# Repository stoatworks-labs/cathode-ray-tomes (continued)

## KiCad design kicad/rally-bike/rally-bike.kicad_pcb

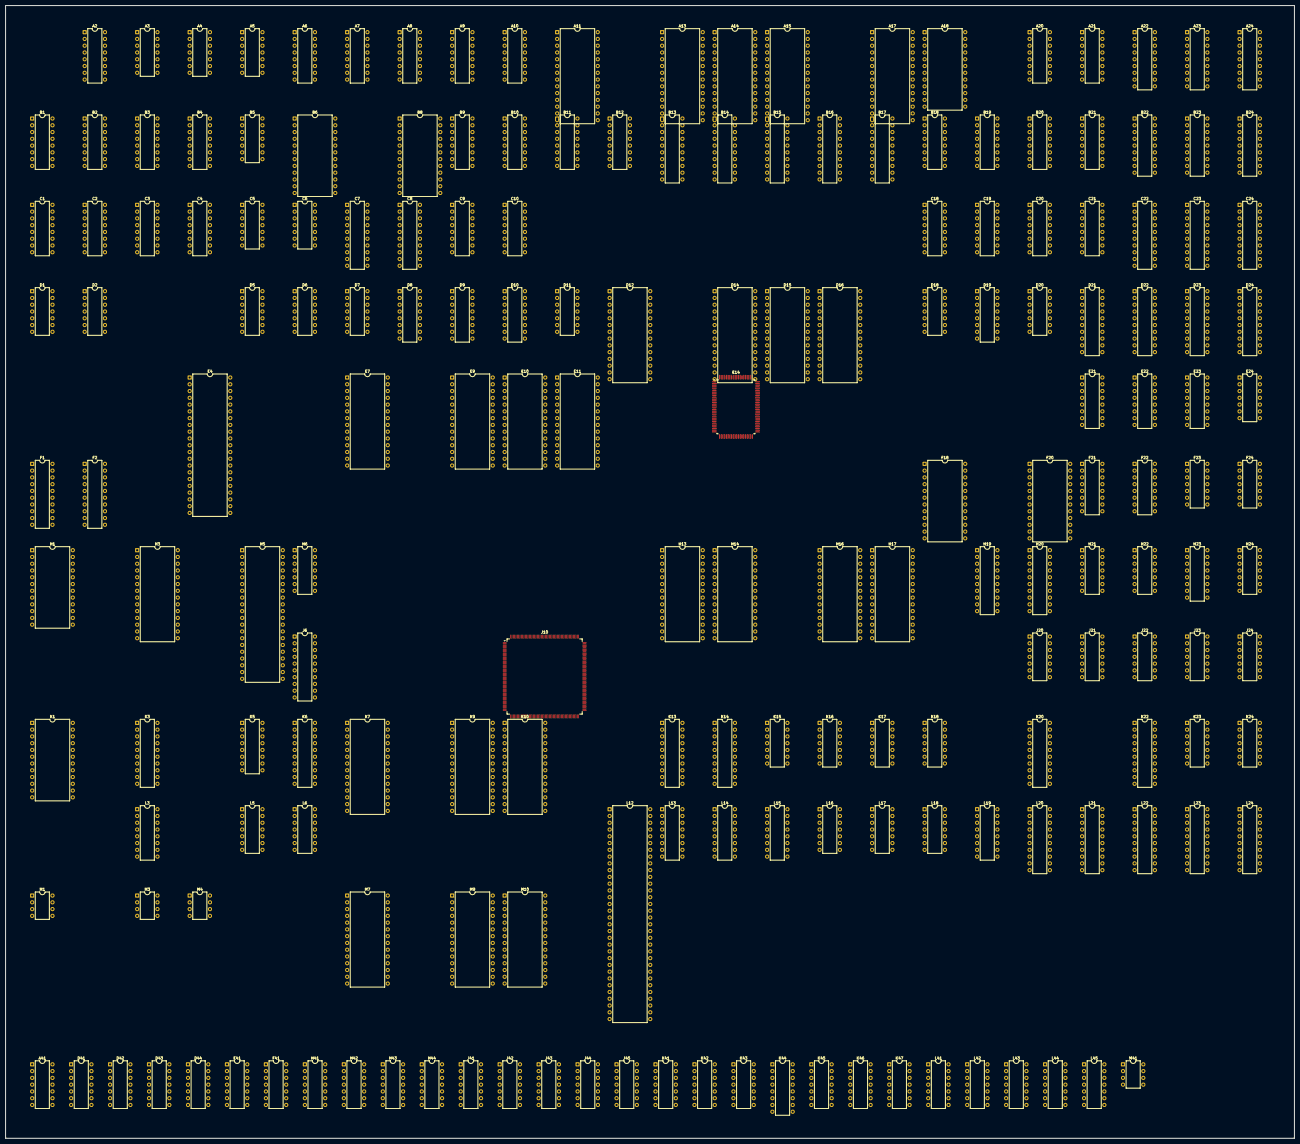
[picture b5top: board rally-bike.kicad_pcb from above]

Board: 2 copper layers, 483.7 x 425.1 mm, 187 parts (0 on the bottom side), 681 nets, no tracks yet.

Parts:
A2: 74LS163; DIP-16_W7.62mm
A3, A5: 74LS393; DIP-14_W7.62mm
A4, A41: 74LS04; DIP-14_W7.62mm
A6, A7, A8, A9, A10, A20, A21: 74LS157; DIP-16_W7.62mm
A11, A13, A14, A15, A17: TC5565; DIP-28_W15.24mm
A18: CXK5816; DIP-24_W15.24mm
A22, A23, A24: AM2148-55PC; DIP-18_W7.62mm
B1, B9, B10: 74LS163; DIP-16_W7.62mm
B2: N82S123N; DIP-16_W7.62mm
B3, B4: N82S129N; DIP-16_W7.62mm
B5: 74LS393; DIP-14_W7.62mm
B6, B8: CXK5816; DIP-24_W15.24mm
B11: 74LS669; DIP-16_W7.62mm
B12: 74LS367; DIP-16_W7.62mm
B13, B14, B15, B16, B17: 74LS374; DIP-20_W7.62mm
B18: 74LS174; DIP-16_W7.62mm
B19: 74LS169; DIP-16_W7.62mm
B20, B21: 74LS157; DIP-16_W7.62mm
B22, B23, B24: AM2148-55PC; DIP-18_W7.62mm
C1, C2: 74LS175; DIP-16_W7.62mm
C3, C9, C10: 74LS174; DIP-16_W7.62mm
C4: 74LS138; DIP-16_W7.62mm
C5: 74LS74; DIP-14_W7.62mm
C6: 74LS08; DIP-14_W7.62mm
C7, C8: 74LS245; DIP-20_W7.62mm
C18: N82S123N; DIP-16_W7.62mm
C19: 74LS169; DIP-16_W7.62mm
C20, C21: 74LS157; DIP-16_W7.62mm
C22, C24: 74LS373; DIP-20_W7.62mm
C23: 74LS374; DIP-20_W7.62mm
D1, D6, D18, D20, D41, D42: 74LS08; DIP-14_W7.62mm
D2, D44: 74LS04; DIP-14_W7.62mm
D5, D7, D43: 74LS32; DIP-14_W7.62mm
D8, D9: 74LS174; DIP-16_W7.62mm
D10: 74LS163; DIP-16_W7.62mm
D11: 74LS74; DIP-14_W7.62mm
D12, D14, D15, D16: 27C512; DIP-28_W15.24mm
D19: 74LS169; DIP-16_W7.62mm
D21: 74LS244; DIP-20_W7.62mm
D22, D24: 74LS373; DIP-20_W7.62mm
D23: 74LS374; DIP-20_W7.62mm
E4: M70H005; DIP-42_W15.24mm
E7, E9, E10, E11: 27C512; DIP-28_W15.24mm
E14: D65024GFO035; PQFP-100_14x20mm_P0.65mm
E21: 74LS139; DIP-16_W7.62mm
E22, E23: 74LS166; DIP-16_W7.62mm
E24, E41: 74LS74; DIP-14_W7.62mm
F1, F2: 74LS245; DIP-20_W7.62mm
F18, F20: HM6116P-3; DIP-24_W15.24mm
F21, F22: 74LS166; DIP-16_W7.62mm
F23, F24, F41: 74LS32; DIP-14_W7.62mm
H1: HM6116P-3; DIP-24_W15.24mm
H3: 27128; DIP-28_W15.24mm
H5: Z80CPU; DIP-40_W15.24mm
H6, H41: 74LS04; DIP-14_W7.62mm
H13, H14, H16, H17: KM62256CLP; DIP-28_W15.24mm
H19, H20: 74LS374; DIP-20_W7.62mm
H21, H44: 74LS08; DIP-14_W7.62mm
H22, H43: 74LS20; DIP-14_W7.62mm
H23: 74LS163; DIP-16_W7.62mm
H24, H42: 74LS74; DIP-14_W7.62mm
J6: 74LS245; DIP-20_W7.62mm
J10: D6508_IR077; PQFP-208_28x28mm_P0.5mm
J20, J44: 74LS04; DIP-14_W7.62mm
J21, J23, J24, J41, J42, J45: 74LS08; DIP-14_W7.62mm
J22, J43: 74LS74; DIP-14_W7.62mm
K1: YM3812-3526; DIP-24_W15.24mm
K3, K13, K14: 74LS245; DIP-20_W7.62mm
K5, K44: 74LS139; DIP-16_W7.62mm
K6: 74LS244; DIP-20_W7.62mm
K7, K9: 27C512; DIP-28_W15.24mm
K10: 6264SL; DIP-28_W15.24mm
K15, K43: 74LS38; DIP-14_W7.62mm
K16, K23, K24, K41, K42, K47: 74LS08; DIP-14_W7.62mm
K17, K45: 74LS32; DIP-14_W7.62mm
K18, K46: 74LS74; DIP-14_W7.62mm
K20, K22: 74LS240; DIP-20_W7.62mm
L3, L13, L14, L15: 74LS138; DIP-16_W7.62mm
L5, L17, L41, L44: 74LS74; DIP-14_W7.62mm
L6, L42: 74LS32; DIP-14_W7.62mm
L12: 68000D; DIP-64_W15.24mm
L16, L45: 74LS08; DIP-14_W7.62mm
L18, L43: 74LS14; DIP-14_W7.62mm
L19: 74LS259; DIP-16_W7.62mm
L20, L21, L22: 74LS240; DIP-20_W7.62mm
L23, L24: 74LS374; DIP-20_W7.62mm
M1: MB3730; DIP-8_W7.62mm
M3: YM3014; DIP-8_W7.62mm
M4, M41: LM358; DIP-8_W7.62mm
M7, M9: 27C256; DIP-28_W15.24mm
M10: 6264SL; DIP-28_W15.24mm

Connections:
/BO0: E14.67, J10.56
/BO1: E14.68, J10.104
/BO2: E14.69, J10.144
/BO3: E14.70, J10.176
/BO6: E14.71, J10.143
/BO7: E14.72, J10.175
/BO8: E14.73, J10.54
/BO9: E14.74, J10.102
/BO10: E14.75, J10.142
/BO11: E14.76, J10.174
/BO12: E14.79, J10.1
/BO13: E14.80, J10.101
/BO14: E14.81, J10.52
/BO15: E14.82, J10.141
/BSPR~CE: C7.19, C8.19, D1.13, D5.13, F24.6
/DCLK1: D2.1, E14.39, H23.13, H24.3, J10.11, L23.11, L24.11
/FOUT0: E14.83, H20.5
/FOUT1: E14.84, H20.2
/FOUT2: E14.85, H20.16
/FOUT3: E14.86, H20.6
/FOUT4: E14.87, H20.19
/FOUT5: E14.88, H20.15
/FOUT6: E14.89, H20.12
/FOUT7: E14.92, H20.9
/FOUT8: E14.93, H19.2
/FOUT9: E14.94, H19.6
/FOUT14: E14.99, H19.5
/FOUT15: E14.100, H19.9
/MAIN_AB0: A6.3, E14.1, E21.2, F1.18, J10.2
/MAIN_AB1: A6.6, E14.2, E21.3, F1.17, J10.58, K7.10, K9.10, K10.10, L12.29, M7.10, M9.10, M10.10
/MAIN_AB2: A6.10, E14.3, F1.16, J10.106, K7.9, K9.9, K10.9, L12.30, M7.9, M9.9, M10.9
/MAIN_AB3: A6.13, E14.4, F1.15, J10.146, K7.8, K9.8, K10.8, L12.31, M7.8, M9.8, M10.8
/MAIN_AB4: A7.3, E14.5, F1.14, K7.7, K9.7, K10.7, L12.32, M7.7, M9.7, M10.7
/MAIN_AB5: A7.6, E14.6, F1.13, K7.6, K9.6, K10.6, L12.33, M7.6, M9.6, M10.6
/MAIN_AB6: A7.10, E14.7, F1.12, K7.5, K9.5, K10.5, L12.34, M7.5, M9.5, M10.5
/MAIN_AB7: A7.13, E14.8, F1.11, K7.4, K9.4, K10.4, L12.35, M7.4, M9.4, M10.4
/MAIN_AB8: A8.3, E14.9, F2.18, K7.3, K9.3, K10.3, L12.36, M7.3, M9.3, M10.3
/MAIN_AB9: A8.6, E14.10, F2.17, K7.25, K9.25, K10.25, L12.37, M7.25, M9.25, M10.25
/MAIN_AB10: A8.10, E14.11, F2.16, K7.24, K9.24, K10.24, L12.38, M7.24, M9.24, M10.24
/MAIN_AB11: E14.12, F2.15, K7.21, K9.21, K10.21, L12.39, M7.21, M9.21, M10.21
/MAIN_AB12: E14.13, F2.14, K7.23, K9.23, K10.23, L12.40, M7.23, M9.23, M10.23
/MAIN_AB13: E14.14, F2.13, K7.2, K9.2, K10.2, L12.41, M7.2, M9.2, M10.2
/MAIN_AB14: F2.12, K7.26, K9.26, L12.42, M7.26, M9.26
/MAIN_AB15: K7.27, K9.27, L12.43, L13.1, M7.27, M9.27
/MAIN_AB16: K7.1, K9.1, L12.44, L13.2
/MAIN_AB17: K7.22, K9.22, L12.45, L13.3
/MAIN_AB18: L12.46, L15.1
/MAIN_AB19: L12.47, L15.2
/MAIN_AB20: L12.48, L15.3
/MAIN_DB0: C7.2, E4.1, E14.20, J10.3, K3.16, K7.11, K13.11, K18.2, L12.5, M7.11, M10.11
/MAIN_DB1: C7.3, E4.2, E14.21, J10.59, K3.17, K7.12, K13.12, L12.4, M7.12, M10.12
/MAIN_DB2: C7.4, E4.3, E14.22, J10.107, K3.18, K7.13, K13.13, L12.3, M7.13, M10.13
/MAIN_DB3: C7.5, E4.4, E14.23, J10.147, K3.11, K7.15, K13.14, L12.2, M7.15, M10.15
/MAIN_DB4: C7.6, E4.5, E14.24, J10.4, K3.12, K7.16, K13.15, L12.1, M7.16, M10.16
/MAIN_DB5: C7.7, E4.6, E14.25, J10.60, K3.13, K7.17, K13.18, L12.64, M7.17, M10.17
/MAIN_DB6: C7.8, E4.7, E14.26, J10.148, K3.14, K7.18, K13.17, L12.63, M7.18, M10.18
/MAIN_DB7: C7.9, E4.8, E14.27, J10.5, K3.15, K7.19, K13.16, L12.62, M7.19, M10.19
/MAIN_DB8: C8.2, E4.9, E14.28, J10.61, K9.11, K10.11, K14.18, L12.61, M9.11
/MAIN_DB9: C8.3, E4.10, E14.29, J10.109, K9.12, K10.12, K14.17, L12.60, M9.12
/MAIN_DB10: C8.4, E4.11, E14.30, K9.13, K10.13, K14.16, L12.59, M9.13
/MAIN_DB11: C8.5, E4.12, E14.31, J10.149, K9.15, K10.15, K14.15, L12.58, M9.15
/MAIN_DB12: C8.6, E14.32, J10.6, K9.16, K10.16, K14.14, L12.57, M9.16
/MAIN_DB13: C8.7, E14.33, J10.62, K9.17, K10.17, K14.13, L12.56, M9.17
/MAIN_DB14: C8.8, E14.34, J10.110, K9.18, K10.18, K14.12, L12.55, M9.18
/MAIN_DB15: C8.9, E14.35, J10.150, K9.19, K10.19, K14.11, L12.54, M9.19
/MR~W: A4.13, D5.12, E14.17, H6.5, H6.11, J10.7, K3.1, K6.8, K10.27, K13.1, K14.1, L12.9, M10.27
/M~DEC4: J10.10, L15.11
/M~LDS: F24.4, K16.4, L3.4, L12.8
/M~Y2: H6.9, K16.2, K17.13, L6.13, L15.13
/SCLK: H6.3, J20.2, K1.24, L5.3, L5.11
/SCU~CS: E14.16, L15.10
/SRST: H5.26, K1.3, K18.5
/SR~WE: B6.21, B8.21, D5.11
/VINT: J20.6, K15.5
/colmix_rgb/LA0: E14.50, F18.8, F20.8
/colmix_rgb/LA1: E14.51, F18.7, F20.7
/colmix_rgb/LA2: E14.52, F18.6, F20.6
/colmix_rgb/LA3: E14.53, F18.5, F20.5
/colmix_rgb/LA4: E14.54, F18.4, F20.4
/colmix_rgb/LA5: E14.55, F18.3, F20.3
/colmix_rgb/LA6: E14.56, F18.2, F20.2
/colmix_rgb/LA7: E14.57, F18.1, F20.1
/colmix_rgb/LA8: E14.58, F18.23, F20.23
/colmix_rgb/LA9: E14.59, F18.22, F20.22
/colmix_rgb/LA10: E14.62, F18.19, F20.19
/colmix_rgb/RGB0: F18.9, K13.9, K23.1
/colmix_rgb/RGB1: F18.10, K13.8, K23.4
/colmix_rgb/RGB2: F18.11, K13.7, K23.9
/colmix_rgb/RGB3: F18.13, K13.6, K23.12
/colmix_rgb/RGB4: F18.14, J23.1, K13.5
/colmix_rgb/RGB5: F18.15, J23.4, K13.2
/colmix_rgb/RGB6: F18.16, J23.9, K13.3
/colmix_rgb/RGB7: F18.17, J23.12, K13.4
/colmix_rgb/RGB8: F20.9, K14.2, K24.1
/colmix_rgb/RGB9: F20.10, K14.3, K24.4
/colmix_rgb/RGB10: F20.11, K14.4, K24.9
/colmix_rgb/RGB11: F20.13, J24.12, K14.5, K24.10, K24.12
/colmix_rgb/RGB12: F20.14, J24.1, K14.6
/colmix_rgb/RGB13: F20.15, J24.4, K14.7
/colmix_rgb/RGB14: F20.16, J24.9, K14.8
/colmix_rgb/RGB15: F20.17, K14.9
/colmix_rgb/SCU~CE: E14.38, K13.19, K14.19
/colmix_rgb/~DVBLK: E14.46, J20.13
/colmix_rgb/~HBLK: E14.43, J21.9
/colmix_rgb/~LOE: E14.63, F18.20, F20.20
/colmix_rgb/~LWE: E14.65, F18.21, F20.21
/io_cabinet/IO0: K20.14, K22.14, L20.18, L21.18, L22.18
/io_cabinet/IO1: K20.7, K22.7, L20.16, L21.16, L22.16
/io_cabinet/IO2: K20.12, K22.12, L20.14, L21.14, L22.14
/io_cabinet/IO3: K20.9, K22.9, L20.12, L21.12, L22.12
/io_cabinet/IO4: K20.18, K22.18, L19.13, L20.9, L21.9, L22.9
/io_cabinet/IO5: K20.3, K22.3, L19.1, L20.7, L21.7, L22.7
/io_cabinet/IO6: K20.16, K22.16, L19.2, L20.5, L21.5, L22.5
/io_cabinet/IO7: K20.5, K22.5, L19.3, L20.3, L21.3, L22.3
/main/IPL: K15.2, L18.8, L18.13
/main/MCLK: L12.15, L17.3, L17.11
/main/MUDS/LDS: K16.6, K17.5, L13.5
/main/M~CLKM5: K17.1, L17.9
/main/M~DEC3: F24.5, L15.12
/main/M~UDS: K16.5, K17.12, L12.7
/main/ROM~CE0: K16.1, L15.15, M7.20, M9.20
/main/ROM~CE1: K7.20, K9.20, K17.2, L15.14, L17.2
/main/~AS: L12.6, L15.4, L15.5
/main/~IPL: L12.24, L12.25, L18.12
/main/~MBNK1: K18.3, L13.14, L16.10
/main/~MDEC0: K16.3, K16.12
/objects/COUNT0: A11.16, B12.3, D12.9, D14.9, D15.9, D16.9
/objects/COUNT1: A11.17, B12.5, D12.8, D14.8, D15.8, D16.8
/objects/COUNT2: A11.18, B12.9, D12.7, D14.7, D15.7, D16.7
/objects/COUNT3: A11.19, B12.7, D12.6, D14.6, D15.6, D16.6
/objects/COUNTQ2: A4.5, C3.7
/objects/Cp1: B13.11, B15.11, C4.14
/objects/Cp2: B14.11, B16.11, C4.13, D11.11
/objects/Cp3: B17.11, C4.12, D11.3
/objects/Cp4: C4.11, C9.9, C10.9
/objects/Cp5: B9.2, B10.2, B11.2, D6.8, D10.2
/objects/FO0: C22.2, D22.2, H20.4
/objects/FO1: C22.5, D22.5, H20.3
/objects/FO2: C22.6, D22.6, H20.17
/objects/FO3: C22.9, D22.9, H20.7
/objects/FO4: C22.19, D22.19, H20.18
/objects/FO5: C22.16, D22.16, H20.14
/objects/FO6: C22.15, D22.15, H20.13
/objects/FO7: C22.12, D22.12, H20.8
/objects/FO8: C24.12, D24.12, H19.3
/objects/FO9: C24.15, D24.15, H19.7
/objects/FO14: C24.16, D24.16, H19.4
/objects/FO15: C24.19, D24.19, H19.8
/objects/FX: A21.1, B21.1, C6.10, C6.12, C21.1, C22.1, C24.1, D8.9, D9.9, D20.2, D20.5, D20.10, D20.13, E24.2, E24.6, F24.9, H22.9
/objects/FX0: A22.14, C22.3, D23.12
/objects/FX1: A22.13, C22.4, D23.15
/objects/FX2: A22.12, C22.7, D23.16
/objects/FX3: A22.11, C22.8, D23.19
/objects/FX4: A23.11, C22.13, D21.3
/objects/FX5: A23.12, C22.14, D21.5
/objects/FX6: A23.13, C22.17, D21.7
/objects/FX7: A23.14, C22.18, D21.9
/objects/FX8: B24.14, C23.2, D24.13
/objects/FX9: B24.13, C23.5, D24.14
/objects/FX10: B24.12, C23.6, D24.17
/objects/FX11: B24.11, C23.9, D24.18
/objects/FY: A20.1, B20.1, C20.1, D18.2, D18.5, D18.10, D18.13, D22.1, D24.1, E24.5, F24.12, H21.5, H21.9, H22.1
/objects/FY0: B22.14, D21.18, D22.3
/objects/FY1: B22.13, D21.16, D22.4
/objects/FY2: B22.12, D21.14, D22.7
/objects/FY3: B22.11, D21.12, D22.8
/objects/FY4: B23.11, D22.13, D23.2
/objects/FY5: B23.12, D22.14, D23.5
/objects/FY6: B23.13, D22.17, D23.6
/objects/FY7: B23.14, D22.18, D23.9
/objects/FY8: A24.14, C23.12, C24.13
/objects/FY9: A24.13, C23.15, C24.14
/objects/FY14: A24.12, C23.16, C24.17
/objects/FY15: A24.11, C23.19, C24.18
/objects/HSPRD'0: A14.11, B14.2, C23.3, D23.3
/objects/HSPRD'1: A14.12, B14.5, C23.4, D23.4
/objects/HSPRD'2: A14.13, B14.6, C23.7, D23.7
/objects/HSPRD'3: A14.15, B14.9, C23.8, D23.8
/objects/HSPRD'4: A14.16, B14.12, C23.13, D23.13
/objects/HSPRD'5: A14.17, B14.15, C23.14, D23.14
/objects/HSPRD'6: A14.18, B14.16
/objects/HSPRD'8: A13.11, B13.19, D12.5, D14.5, D15.5, D16.5
/objects/HSPRD'9: A13.12, B13.16, D12.4, D14.4, D15.4, D16.4
/objects/HSPRD'10: A13.13, B13.15, D12.3, D14.3, D15.3, D16.3
/objects/HSPRD'11: A13.15, B13.12, D12.25, D14.25, D15.25, D16.25
/objects/HSPRD'12: A13.16, B13.9, D12.24, D14.24, D15.24, D16.24
/objects/HSPRD'13: A13.17, B13.6, D12.21, D14.21, D15.21, D16.21
/objects/HSPRD'14: A13.18, B13.5, D12.23, D14.23, D15.23, D16.23
/objects/HSPRD'15: A13.19, B13.2, D12.2, D14.2, D15.2, D16.2
/objects/LATCH1: C1.6, F23.1
/objects/Obj_fms/1: B3.12, C3.3
/objects/Obj_fms/2: B3.11, C3.14
/objects/Obj_fms/3: B3.10, C3.4
/objects/Obj_fms/4: B3.9, C3.6
/objects/Obj_fms/5: B4.12, C3.13
/objects/Obj_fms/6: B4.11, C3.11
/objects/Obj_fms/DC~PE: A2.9, B1.9, C2.14
/objects/Obj_fms/MRST2: A3.2, A3.12, D5.3
/objects/Obj_fms/T0: A3.3, B3.5, B4.5
/objects/Obj_fms/T1: A3.4, B3.6, B4.6
/objects/Obj_fms/T2: A3.5, B3.7, B4.7
/objects/Obj_fms/T3: A3.6, A3.13, B3.4, B4.4
/objects/Obj_fms/T4: A3.11, B3.3, B4.3
/objects/Obj_fms/T5: A3.10, B3.2, B4.2
/objects/Obj_fms/T6: A3.9, B3.1, B4.1
/objects/Obj_fms/T7: A3.8, B3.15, B4.15
/objects/Obj_fms/~CLEAR: C4.9, C5.1, D6.13
/objects/Obj_fms/~SET: C4.10, C5.4, D6.9
/objects/SCD~PE: B19.9, C1.14, C19.9, D7.2, D19.9
/objects/SCM0: D9.14, E4.41
/objects/SCM0': A20.14, A21.14, D9.15
/objects/SCM1: D9.3, E4.40
/objects/SCM1': B20.2, B21.2, D9.2
/objects/SCM2: D9.4, E4.39
/objects/SCM2': B20.5, B21.5, D9.5
/objects/SCM3: D8.4, E4.38
/objects/SCM3': B20.11, B21.11, D8.5
/objects/SCM4: D8.3, E4.37
/objects/SCM4': B20.14, B21.14, D8.2
/objects/SCM5: D8.6, E4.36
/objects/SCM5': C20.2, C21.2, D8.7
/objects/SCM6: A9.13, E4.35
/objects/SCM7: A10.3, E4.34
/objects/SCM8: A10.6, E4.33
/objects/SCM9: A10.10, E4.32
/objects/SCM10: A10.13, E4.31
/objects/SCX0: D9.11, E4.28
/objects/SCX0': A20.2, A21.2, D9.10
/objects/SCX1: D9.6, E4.27
/objects/SCX1': A20.5, A21.5, D9.7
/objects/SCX2: D9.13, E4.26
/objects/SCX2': A20.11, A21.11, D9.12
/objects/SHIFTR: F23.6, H22.2, H22.13
/objects/SPR'~OE: B12.1, B12.15, B13.1, B14.1, B15.1, B16.1, B17.1, C1.2
/objects/SPRAM~OE: A11.22, A13.22, A14.22, A15.22, A17.22, C1.3
/objects/SPRD'0: A17.11, B16.9, C6.9, H21.4
/objects/SPRD'1: A17.12, B16.12, C6.13, H21.10
/objects/SPRD'2: A17.13, B17.2, B19.3
/objects/SPRD'3: A17.15, B17.5, B19.4
/objects/SPRD'4: A17.16, B17.6, B19.5
/objects/SPRD'5: A17.17, B17.9, B19.6
/objects/SPRD'6: A17.18, B17.12, C19.3
/objects/SPRD'7: A17.19, B17.15, C19.4
/objects/SPRD'8: A15.11, B15.5, D12.26, D14.26, D15.26, D16.26
/objects/SPRD'9: A15.12, B15.6, D12.27, D14.27, D15.27, D16.27
/objects/SPRD'10: A15.13, B15.9, D12.1, D14.1, D15.1, D16.1
/objects/SPRD'11: A15.15, B15.12
/objects/SPRD'12: A15.16, B15.15
/objects/SPRD'13: A11.11, B17.16, C19.5
/objects/SPRD'14: A11.12, B17.19, C19.6
/objects/SPRD'15: A15.19, B16.5, E24.12
/objects/SPRDB15: A11.13, B12.13, D19.3
/objects/SPRDQ2: A20.3, A21.3, B19.14
/objects/SPRDQ3: A20.6, A21.6, B19.13
/objects/SPRDQ4: A20.10, A21.10, B19.12
/objects/SPRDQ5: A20.13, A21.13, B19.11
/objects/SPRDQ6: B20.3, B21.3, C19.14
/objects/SPRDQ7: B20.6, B21.6, C19.13
/objects/SPRDQ13: B20.10, B21.10, C19.12
/objects/SPRDQ14: B20.13, B21.13, C19.11
/objects/SPROMA0: C1.10, D12.10, D14.10, D15.10, D16.10
/objects/SPRQ15: C20.3, C21.3, D19.14
/objects/SPR~CEP: C1.11, C6.2
/objects/SPR~CET: C2.11, C6.1
/objects/SPR~WEX: A22.10, A23.10, A24.10, C23.1, D21.19, H21.11
/objects/SPR~WEY: B22.10, B23.10, B24.10, D21.1, D23.1, H21.3
/objects/SRCLK: A2.2, B1.2, B19.2, C1.9, C2.9, C19.2, D2.3, D7.1, D19.2, E22.7, E23.7, F21.7, F22.7, H23.14
/objects/VBLK: A4.3, A5.2, A5.12, A6.1, A7.1, A8.1, A9.1, A10.1, B5.2, C6.4, D5.2, J21.6
/objects/WE: C2.10, H22.5, H22.10
/objects/XY0: B20.4, B22.5, B23.5, B24.5
/objects/XY1: B20.7, B22.6, B23.6, B24.6
/objects/XY2: B20.9, B22.7, B23.7, B24.7
/objects/XY3: A20.12, B22.4, B23.4, B24.4
/objects/XY4: A20.9, B22.3, B23.3, B24.3
/objects/XY5: A20.7, B22.2, B23.2, B24.2
/objects/XY6: A20.4, B22.1, B23.1, B24.1
/objects/XY7: B20.12, B22.17, B23.17, B24.17
/objects/XY8: B22.16, B23.16, B24.16, C20.4
/objects/XY9: A22.5, A23.5, A24.5, B21.4
/objects/XY10: A22.6, A23.6, A24.6, B21.7
/objects/XY11: A22.7, A23.7, A24.7, B21.9
/objects/XY12: A21.12, A22.4, A23.4, A24.4
/objects/XY13: A21.9, A22.3, A23.3, A24.3
/objects/XY14: A21.7, A22.2, A23.2, A24.2
/objects/XY15: A21.4, A22.1, A23.1, A24.1
/objects/XY16: A22.17, A23.17, A24.17, B21.12
/objects/XY17: A22.16, A23.16, A24.16, C21.4
/objects/obj_memories/D0: A18.9, B18.6, C18.1
/objects/obj_memories/D1: A18.10, B18.4, C18.2
/objects/obj_memories/D2: A18.11, B18.3, C18.3
/objects/obj_memories/D3: A18.13, B18.13, C18.4
/objects/obj_memories/D4: A18.14, B18.11, C18.5
/objects/obj_memories/MRW: A4.12, A8.13, C7.1, C8.1
/objects/obj_memories/R~W: A11.27, A13.27, A14.27, A15.27, A17.27, A18.21, C18.15, D6.6
/objects/obj_memories/SCY0: A9.3, E4.25
/objects/obj_memories/SCY1: A9.6, E4.24
/objects/obj_memories/SCY2: A9.10, E4.23
/objects/obj_memories/SPRA0: A6.4, B6.8, B8.8
/objects/obj_memories/SPRA1: A6.7, B6.7, B8.7
/objects/obj_memories/SPRA2: A6.9, B6.6, B8.6
/objects/obj_memories/SPRA3: A6.12, B6.5, B8.5
/objects/obj_memories/SPRA4: A7.4, B6.4, B8.4
/objects/obj_memories/SPRA5: A7.7, B6.3, B8.3
/objects/obj_memories/SPRA6: A7.9, B6.2, B8.2
/objects/obj_memories/SPRA7: A7.12, B6.1, B8.1
/objects/obj_memories/SPRA8: A8.4, B6.23, B8.23
/objects/obj_memories/SPRA9: A8.7, B6.22, B8.22
/objects/obj_memories/SPRA10: A8.9, B6.19, B8.19
/objects/obj_memories/SPRAMA0: A9.4, A11.10, A13.10, A14.10, A15.10, A17.10, A18.8
/objects/obj_memories/SPRAMA1: A9.7, A11.9, A13.9, A14.9, A15.9, A17.9, A18.7
/objects/obj_memories/SPRAMA2: A9.9, A11.8, A13.8, A14.8, A15.8, A17.8, A18.6
/objects/obj_memories/SPRAMA3: A9.12, A11.7, A13.7, A14.7, A15.7, A17.7, A18.5
/objects/obj_memories/SPRAMA4: A10.4, A11.6, A13.6, A14.6, A15.6, A17.6, A18.4
/objects/obj_memories/SPRAMA5: A10.7, A11.5, A13.5, A14.5, A15.5, A17.5, A18.3
/objects/obj_memories/SPRAMA6: A10.9, A11.4, A13.4, A14.4, A15.4, A17.4, A18.2
/objects/obj_memories/SPRAMA7: A10.12, A11.3, A13.3, A14.3, A15.3, A17.3, A18.1
/objects/obj_memories/SPRAMA8: A11.25, A13.25, A14.25, A15.25, A17.25, B18.7, C18.10
/objects/obj_memories/SPRAMA9: A11.24, A13.24, A14.24, A15.24, A17.24, B18.5, C18.11
/objects/obj_memories/SPRAMA10: A11.21, A13.21, A14.21, A15.21, A17.21, B18.2, C18.12
/objects/obj_memories/SPRAMA11: A11.23, A13.23, A14.23, A15.23, A17.23, B18.12, C18.13
/objects/obj_memories/SPRAMA12: A11.2, A13.2, A14.2, A15.2, A17.2, B18.10, C18.14
/objects/obj_memories/SPRAM~OE2: A4.8, A18.20
/objects/obj_memories/SPRD0: B6.9, B13.3, B14.3, C7.18
/objects/obj_memories/SPRD1: B6.10, B13.4, B14.4, C7.17
/objects/obj_memories/SPRD2: B6.11, B13.7, B14.7, C7.16
/objects/obj_memories/SPRD3: B6.13, B13.8, B14.8, C7.15
/objects/obj_memories/SPRD4: B6.14, B13.13, B14.13, C7.14
/objects/obj_memories/SPRD5: B6.15, B13.14, B14.14, C7.13
/objects/obj_memories/SPRD6: B6.16, B13.17, B14.17, C7.12
/objects/obj_memories/SPRD7: B6.17, B13.18, B17.3, C7.11, C9.3
/objects/obj_memories/SPRD8: B8.9, B15.4, B16.4, B17.4, C8.18, C9.14
/objects/obj_memories/SPRD9: B8.10, B15.7, B17.7, C8.17, C9.13, D11.12
/objects/obj_memories/SPRD10: B8.11, B15.8, B16.8, B17.8, C8.16, C9.4
/objects/obj_memories/SPRD11: B8.13, B15.13, B16.13, B17.13, C8.15, C10.11
/objects/obj_memories/SPRD12: B8.14, B15.14, B17.14, C8.14, C10.6
/objects/obj_memories/SPRD13: B8.15, B17.17, C8.13, C10.3
/objects/obj_memories/SPRD14: B8.16, B17.18, C8.12, C10.14
/objects/obj_memories/SPRD15: B8.17, C8.11, C10.13, D11.2
/objects/obj_memories/SPRD15'Q: D5.9, D10.14
/objects/obj_memories/SPRDQ15: B12.14, D11.5
/objects/obj_memories/SR~OE: A8.12, B6.20, B8.20
/objects/obj_memories/~SA: E4.22, E21.7
/objects/obj_memories/~WA: E4.20, E21.6
/objects/obj_memories/~WX: E4.13, E21.4
/objects/obj_memories/~WY: E4.16, E21.5
/objects/obj_pxl/LATCH: C23.11, D23.11, E22.15, E23.15, F21.15, F22.15, F23.3
/objects/obj_pxl/SR0: D18.4, D20.4, F22.13, F23.10
/objects/obj_pxl/SR1: D18.9, D20.9, F21.13, F23.9
/objects/obj_pxl/SR2: D18.12, D20.12, E23.13, F23.13
/objects/obj_pxl/SR3: D18.1, D20.1, E22.13, F23.12
/objects/~CLR: B18.9, D6.11
/objects/~COUNTQ4: A4.10, D5.10, D6.10
/objects/~DCLK2: A4.1, C3.9, C4.4, C22.11, C24.11, D2.2, D22.11, D24.11, E4.15, F24.10, F24.13, H19.11, H20.11
/objects/~LD: B9.9, B10.9, B11.9, C5.6, D10.9
/objects/~RW: C2.3, D6.5
/objects/~SPRD'15: B19.1, C19.1, D19.1, E24.8
/objects/~SRCLK: D2.4, H22.4, H22.12
/objects/~WEY: H21.1, H22.6
/scroll/BCMA0: H13.10, H14.10, H16.10, H17.10, J10.12
/scroll/BCMA1: H13.9, H14.9, H16.9, H17.9, J10.66
/scroll/BCMA2: H13.8, H14.8, H16.8, H17.8, J10.112
/scroll/BCMA3: H13.7, H14.7, H16.7, H17.7, J10.13
/scroll/BCMA4: H13.6, H14.6, H16.6, H17.6, J10.67
/scroll/BCMA5: H13.5, H14.5, H16.5, H17.5, J10.113
/scroll/BCMA6: H13.4, H14.4, H16.4, H17.4, J10.151
/scroll/BCMA7: H13.3, H14.3, H16.3, H17.3, J10.14
/scroll/BCMA8: H13.25, H14.25, H16.25, H17.25, J10.68
/scroll/BCMA9: H13.24, H14.24, H16.24, H17.24, J10.114
/scroll/BCMA10: H13.21, H14.21, H16.21, H17.21, J10.152
/scroll/BCMA11: H13.23, H14.23, H16.23, H17.23, J10.16
/scroll/BCMA12: H13.2, H14.2, H16.2, H17.2, J10.70
/scroll/BCMA13: H13.26, H14.26, H16.26, H17.26, J10.116
/scroll/BCURAM~OE: H13.22, H14.22, H16.22, H17.22, J10.17
/scroll/BCURAM~WE: H13.27, H14.27, H16.27, H17.27, J10.18
/scroll/BCUROM~OE: E7.22, E9.22, E10.22, E11.22, J10.100
/scroll/GA0: E7.10, E9.10, E10.10, E11.10, J10.28
/scroll/GA1: E7.9, E9.9, E10.9, E11.9, J10.80
/scroll/GA2: E7.8, E9.8, E10.8, E11.8, J10.27
/scroll/GA3: E7.7, E9.7, E10.7, E11.7, J10.124
/scroll/GA4: E7.6, E9.6, E10.6, E11.6, J10.79
/scroll/GA5: E7.5, E9.5, E10.5, E11.5, J10.26
/scroll/GA6: E7.4, E9.4, E10.4, E11.4, J10.99
/scroll/GA7: E7.3, E9.3, E10.3, E11.3, J10.50
/scroll/GA8: E7.25, E9.25, E10.25, E11.25, J10.47
/scroll/GA9: E7.24, E9.24, E10.24, E11.24, J10.138
/scroll/GA10: E7.21, E9.21, E10.21, E11.21, J10.97
/scroll/GA11: E7.23, E9.23, E10.23, E11.23, J10.48
/scroll/GA12: E7.2, E9.2, E10.2, E11.2, J10.172
/scroll/GA13: E7.26, E9.26, E10.26, E11.26, J10.139
/scroll/GA14: E7.27, E9.27, E10.27, E11.27, J10.98
/scroll/GA15: E7.1, E9.1, E10.1, E11.1, J10.49
/scroll/GD0: E9.11, J10.89
/scroll/GD1: E9.12, J10.131
/scroll/GD2: E9.13, J10.40
/scroll/GD3: E9.15, J10.90
/scroll/GD4: E9.16, J10.132
/scroll/GD5: E9.17, J10.166
/scroll/GD6: E9.18, J10.41
/scroll/GD7: E9.19, J10.91
/scroll/GD8: E7.11, J10.34
/scroll/GD9: E7.12, J10.86
/scroll/GD10: E7.13, J10.35
/scroll/GD11: E7.15, J10.36
/scroll/GD12: E7.16, J10.37
/scroll/GD13: E7.17, J10.38
/scroll/GD14: E7.18, J10.88
/scroll/GD15: E7.19, J10.39
/scroll/GD16: E10.11, J10.32
/scroll/GD17: E10.12, J10.84
/scroll/GD18: E10.13, J10.128
/scroll/GD19: E10.15, J10.164
/scroll/GD20: E10.16, J10.33
/scroll/GD21: E10.17, J10.85
/scroll/GD22: E10.18, J10.129
/scroll/GD23: E10.19, J10.165
/scroll/GD24: E11.11, J10.30
/scroll/GD25: E11.12, J10.82
/scroll/GD26: E11.13, J10.126
/scroll/GD27: E11.15, J10.162
/scroll/GD28: E11.16, J10.31
/scroll/GD29: E11.17, J10.83
/scroll/GD30: E11.18, J10.127
/scroll/GD31: E11.19, J10.163
/scroll/M0: H14.11, J10.19
/scroll/M1: H14.12, J10.72
/scroll/M2: H14.13, J10.117
/scroll/M3: H14.15, J10.154
/scroll/M4: H14.16, J10.20
/scroll/M5: H14.17, J10.73
/scroll/M6: H14.18, J10.118
/scroll/M7: H14.19, J10.155
/scroll/M8: H16.11, J10.21
/scroll/M9: H16.12, J10.74
/scroll/M10: H16.13, J10.119
/scroll/M11: H16.15, J10.156
/scroll/M12: H16.16, J10.23
/scroll/M13: H16.17, J10.76
/scroll/M14: H16.18, J10.121
/scroll/M15: H16.19, J10.158
/scroll/M16: H13.11, J10.24
/scroll/M17: H13.12, J10.77
/scroll/M18: H13.13, J10.122
/scroll/M19: H13.15, J10.159
/scroll/M20: H13.16, J10.25
/scroll/M21: H13.17, J10.123
/scroll/M22: H13.18, J10.160
/scroll/M23: H13.19, J10.29
/scroll/M24: H17.11, J10.22
/scroll/M25: H17.12, J10.75
/sound/MO: K1.21, M3.4
/sound/MP: M3.8, M4.1, M4.2
/sound/SH: K1.20, M3.3
/sound/SHB~CE: F1.19, F2.19, K3.19, L6.3
/sound/SND_A0: F1.2, H1.8, H3.10, H5.30, K1.4
/sound/SND_A1: F1.3, H1.7, H3.9, H5.31
/sound/SND_A2: F1.4, H1.6, H3.8, H5.32
/sound/SND_A3: F1.5, H1.5, H3.7, H5.33
/sound/SND_A4: F1.6, H1.4, H3.6, H5.34, L14.1
/sound/SND_A5: F1.7, H1.3, H3.5, H5.35, L14.2
/sound/SND_A6: F1.8, H1.2, H3.4, H5.36, L14.3
/sound/SND_A7: F1.9, H1.1, H3.3, H5.37
/sound/SND_A8: F2.2, H1.23, H3.25, H5.38
/sound/SND_A9: F2.3, H1.22, H3.24, H5.39
/sound/SND_A10: F2.4, H1.19, H3.21, H5.40
/sound/SND_A11: F2.5, H3.23, H5.1
/sound/SND_A12: F2.6, H3.2, H5.2
/sound/SND_A13: F2.7, H3.26, H5.3
/sound/SND_A14: F2.8, H5.4
/sound/SND_A15: F2.9, H5.5, K5.2
/sound/SND_D0: H1.9, H3.11, H5.14, J6.4, K3.4
/sound/SND_D1: H1.10, H3.12, H5.15, J6.5, K3.3
/sound/SND_D2: H1.11, H3.13, H5.12, J6.2, K3.2
/sound/SND_D3: H1.13, H3.15, H5.8, J6.9, K3.9
/sound/SND_D4: H1.14, H3.16, H5.7, J6.8, K3.8
/sound/SND_D5: H1.15, H3.17, H5.9, J6.7, K3.7
/sound/SND_D6: H1.16, H3.18, H5.10, J6.6, K3.6
/sound/SND_D7: H1.17, H3.19, H5.13, J6.3, K3.5
/sound/S~CE: H3.20, K5.4
/sound/S~INT: H5.16, K1.2
/sound/S~IORQ: H5.20, K6.16, L14.4
/sound/S~M1: H5.27, L14.6
/sound/S~MREQ: H5.19, K5.1, K6.18
/sound/S~RD: H1.20, H3.22, H5.21, J6.1, K1.6, K6.14
/sound/S~WR: H1.21, H5.22, J6.19, K1.5, K6.12
/sound/YM_D0: J6.16, K1.10
/sound/YM_D1: J6.15, K1.11
/sound/YM_D2: J6.18, K1.13
/sound/YM_D3: J6.11, K1.14
/sound/YM_D4: J6.12, K1.15
/sound/YM_D5: J6.13, K1.16
/sound/YM_D6: J6.14, K1.17
/sound/YM_D7: J6.17, K1.18
/sound/YM~CS: K1.7, L14.9
/sound/~BUSACK: H5.23, L5.2, L6.1
/sound/ØSY: K1.23, M3.5
/~ACK: E14.19, J10.63
/~BUSACKQ: L5.5, L5.12, L6.5
/~BUSRQ: H5.25, L6.2, L6.4, L15.9
/~DIPSW-1: K20.1, K20.19, L14.10
/~DIPSW-2: K22.1, K22.19, L14.11
/~DTACK: K6.1, L6.6, L6.9
/~E_COIN: L14.12, L19.14
/~HS: E14.42, H6.13, H24.2, J21.1
/~KEY-1P: L14.13, L20.1, L20.19
/~KEY-2P: L14.15, L21.1, L21.19
/~KEY-TILT: L14.14, L22.1, L22.19
/~LDS: E14.18, J10.9
/~LX/~CY: C6.5, E4.14, E4.18, J10.111
/~MBNK0: D1.12, E21.1, L13.15
/~RESET: E14.36, J10.64, K18.1, L18.2, L19.15
/~VBLK: E14.45, J21.5, J21.12
/~VS: E4.17, E14.44, J10.65, J21.2
unnamed: A2.14, B2.10
unnamed: A2.13, B2.11
unnamed: A2.12, B2.12
unnamed: A2.11, B2.13
unnamed: A2.15, B1.7, B1.10
unnamed: A3.1, A4.2
unnamed: A4.9, D5.8, D6.4
unnamed: A5.3, A6.2
unnamed: A5.4, A6.5
unnamed: A5.5, A6.11
unnamed: A5.6, A5.13, A6.14
unnamed: A4.6, A5.1
unnamed: A5.11, A7.2
unnamed: A5.10, A7.5
unnamed: A5.9, A7.11
unnamed: A5.8, A7.14, B5.1
unnamed: A8.2, B5.3
unnamed: A8.5, B5.4
unnamed: A8.11, B5.5
unnamed: A9.2, B9.14
unnamed: A9.5, B9.13
unnamed: A9.11, B9.12
unnamed: A9.14, B9.11
unnamed: A10.2, B10.14
unnamed: A10.5, B10.13
unnamed: A10.11, B10.12
unnamed: A10.14, B10.11
unnamed: B1.14, B2.14
unnamed: B2.1, C1.4
unnamed: B2.2, C1.5
unnamed: B2.3, C1.13
unnamed: B2.4, C1.12
unnamed: B2.5, C2.5
unnamed: B2.6, C2.4
unnamed: B2.7, C2.12
unnamed: B2.9, C2.13
unnamed: B9.3, C9.2
unnamed: B9.4, C9.15
unnamed: B9.5, C9.12
unnamed: B9.6, C9.5
unnamed: B9.15, B10.7, B10.10
unnamed: B10.3, C10.10
unnamed: B10.4, C10.7
unnamed: B10.5, C10.2
unnamed: B10.6, C10.15
unnamed: B10.15, D10.7, D10.10
unnamed: B11.3, B11.4, B11.5, B11.6, D11.9
unnamed: B11.14, B12.2
unnamed: B11.13, B12.4
unnamed: B11.12, B12.10
unnamed: B11.11, B12.6
unnamed: B11.1, D11.8
unnamed: B19.7, B19.10, C6.3
unnamed: B19.15, C19.7, C19.10
unnamed: C1.1, C2.1, C6.6
unnamed: C2.6, D6.12
unnamed: C3.2, C4.1
unnamed: C3.5, C4.3
unnamed: C3.10, D5.1
unnamed: A4.11, C3.12
unnamed: C3.15, C4.2
unnamed: A4.4, C3.1
unnamed: C10.12, D10.3
unnamed: C19.15, D19.7, D19.10
unnamed: C6.8, C23.17
unnamed: C6.11, C23.18
unnamed: D1.11, L16.12
unnamed: D12.11, F22.2
unnamed: D12.12, F22.3
unnamed: D12.13, F22.4
unnamed: D12.15, F22.5
unnamed: D12.16, F22.10
unnamed: D12.17, F22.11
unnamed: D12.18, F22.12
unnamed: D12.19, F22.14
unnamed: D14.11, F21.2
unnamed: D14.12, F21.3
unnamed: D14.13, F21.4
unnamed: D14.15, F21.5
unnamed: D14.16, F21.10
unnamed: D14.17, F21.11
unnamed: D14.18, F21.12
unnamed: D14.19, F21.14
unnamed: D15.11, E23.2
unnamed: D15.12, E23.3
unnamed: D15.13, E23.4
unnamed: D15.15, E23.5
unnamed: D15.16, E23.10
unnamed: D15.17, E23.11
unnamed: D15.18, E23.12
unnamed: D15.19, E23.14
unnamed: D16.11, E22.2
unnamed: D16.12, E22.3
unnamed: D16.13, E22.4
unnamed: D16.15, E22.5
unnamed: D16.16, E22.10
unnamed: D16.17, E22.11
unnamed: D16.18, E22.12
unnamed: D16.19, E22.14
unnamed: D18.3, D21.2
unnamed: D20.8, D21.11
unnamed: D18.11, D21.4
unnamed: D20.6, D21.13
unnamed: D18.6, D21.6
unnamed: D20.11, D21.15
unnamed: D18.8, D21.8
unnamed: D20.3, D21.17
unnamed: D23.17, H21.6
unnamed: D23.18, H21.8
unnamed: E14.37, J20.5
unnamed: E24.3, H24.5
unnamed: D7.3, E24.11
unnamed: F23.5, F23.8
unnamed: F23.4, F23.11
unnamed: F24.8, H21.12
unnamed: F24.11, H21.2
unnamed: H1.18, K5.5
unnamed: H5.6, H6.4
unnamed: H21.13, H22.8
unnamed: H23.12, J20.1
unnamed: J20.11, J20.12
unnamed: J21.8, J24.2, J24.5, J24.10, J24.13, K24.2, K24.5, K24.13
unnamed: J21.10, J21.11
unnamed: H6.12, J22.3
unnamed: J20.10, J22.2
unnamed: J21.13, J22.5
unnamed: K6.2, L6.12
unnamed: H6.6, K6.6
unnamed: H6.10, K10.22, M10.22
unnamed: K15.10, K15.13, L18.1, L18.4
unnamed: K16.11, K17.4
unnamed: K17.6, L16.2
unnamed: L5.9, L6.10
unnamed: L12.10, L16.6
unnamed: L3.1, L12.28
unnamed: L3.2, L12.27
unnamed: L3.3, L12.26
unnamed: K15.8, L12.17
unnamed: K15.3, K15.6, L12.23
unnamed: L3.7, L12.21
unnamed: L13.4, L15.7
unnamed: L16.1, L16.8
unnamed: L16.3, L16.5
unnamed: L6.8, L16.9
unnamed: L16.4, L16.11
unnamed: L17.5, L17.12
unnamed: L18.5, L18.10
unnamed: K23.6, L23.3
unnamed: K23.3, L23.4
unnamed: J23.6, L23.7
unnamed: J23.3, L23.8
unnamed: J23.11, L23.13
unnamed: J23.8, L23.14
unnamed: K23.11, L23.17
unnamed: K23.8, L23.18
unnamed: K24.6, L24.3
unnamed: K24.3, L24.4
unnamed: J24.6, L24.7
unnamed: J24.3, L24.8
unnamed: J24.11, L24.13
unnamed: J24.8, L24.14
unnamed: J23.2, J23.5, J23.10, J23.13, K23.2, K23.5, K23.10, K23.13, K24.11, L24.17
unnamed: K24.8, L24.18
unnamed: M3.2, M4.5
unnamed: M3.7, M4.3
unnamed: M4.6, M4.7
unnamed: L18.9, L18.11
VCC: A2.1, A2.6, A2.7, A2.10, A3.14, A5.14, A11.26, A13.26, A14.26, A15.26, A17.26, A18.24, A22.18, A23.18, A24.18, A41.14, B1.1, B2.16, B3.16, B4.16, B5.14, B6.24, B8.24, B9.1, B9.7, B9.10, B10.1, B11.16, B12.16, B18.1, B19.16, B22.18, B23.18, B24.18, C4.6, C5.14, C6.14, C9.1, C10.1, C18.16, C19.16, C22.20, C24.20, D1.14, D5.14, D6.14, D7.14, D8.1, D9.1, D10.1, D11.1, D11.4, D11.10, D11.13, D11.14, D12.28, D14.28, D15.28, D16.28, D18.14, D19.16, D21.20, D22.20, D24.20, D41.14, D42.14, D43.14, D44.14, E4.19, E4.42, E7.28, E9.28, E10.28, E11.28, E14.41, E14.47, E14.91, E21.16, E22.9, E22.16, E23.9, E23.16, E24.1, E24.4, E24.10, E24.13, E41.14, F2.11, F18.24, F20.24, F21.9, F21.16, F22.9, F22.16, F23.14, F41.14, H1.24, H3.1, H3.27, H3.28, H5.11, H5.17, H5.24, H13.28, H14.28, H16.28, H17.28, H23.1, H23.3, H23.4, H23.5, H23.6, H23.7, H23.9, H23.10, H24.1, H24.4, H41.14, H42.14, H43.14, H44.14, J10.145, J10.153, J10.157, J10.161, J10.169, J21.4, J22.1, J22.4, J41.14, J42.14, J43.14, J44.14, J45.14, K1.1, K6.4, K6.20, K7.28, K9.28, K10.14, K10.26, K10.28, K15.1, K15.4, K15.9, K15.12, K16.10, K18.4, K20.20, K22.20, K41.14, K42.14, K43.14, K44.16, K45.14, K46.14, K47.14, L3.6, L5.1, L5.4, L5.10, L5.13, L12.14, L12.49, L13.6, L15.6, L17.1, L17.4, L17.10, L17.13, L19.16, L20.20, L21.20, L22.20, L41.14, L42.14, L43.14, L44.14, L45.14, M3.1, M7.1, M7.28, M9.1, M9.28, M10.14, M10.26, M10.28, M41.8
VSS: A2.3, A2.4, A2.5, A3.7, A5.7, A6.15, A7.15, A8.14, A8.15, A9.15, A10.15, A11.20, A11.28, A13.20, A13.28, A14.20, A14.28, A15.20, A15.28, A17.20, A17.28, A18.12, A18.18, A18.19, A18.22, A18.23, A20.15, A21.15, A22.8, A22.9, A22.15, A23.8, A23.9, A23.15, A24.8, A24.9, A24.15, A41.7, B1.3, B1.4, B1.5, B1.6, B2.8, B2.15, B3.8, B3.13, B3.14, B4.8, B4.13, B4.14, B5.7, B6.12, B6.18, B8.12, B8.18, B11.7, B11.10, B12.8, B19.8, B20.15, B21.15, B22.8, B22.9, B22.15, B23.8, B23.9, B23.15, B24.8, B24.9, B24.15, C5.3, C5.7, C6.7, C18.8, C19.8, C20.15, C21.15, C22.10, C24.10, D1.7, D5.7, D6.7, D7.7, D11.7, D12.14, D12.20, D12.22, D14.14, D14.20, D14.22, D15.14, D15.20, D15.22, D16.14, D16.20, D16.22, D18.7, D19.8, D21.10, D22.10, D24.10, D41.7, D42.7, D43.7, D44.7, E4.21, E4.29, E7.14, E7.20, E9.14, E9.20, E10.14, E10.20, E11.14, E11.20, E14.15, E14.40, E14.49, E14.66, E14.77, E14.78, E14.90, E14.95, E14.96, E14.97, E14.98, E21.8, E22.1, E22.6, E22.8, E23.1, E23.6, E23.8, E41.7, F1.1, F2.1, F18.12, F18.18, F20.12, F20.18, F21.1, F21.6, F21.8, F22.1, F22.6, F22.8, F23.2, F23.7, F41.7, H1.12, H3.14, H5.29, H13.1, H13.14, H13.20, H14.1, H14.14, H14.20, H16.1, H16.14, H16.20, H17.1, H17.14, H17.20, H19.1, H20.1, H41.7, H42.7, H43.7, H44.7, J10.8, J10.42, J10.43, J10.44, J10.45, J10.46, J10.53, J10.57, J10.69, J10.71, J10.78, J10.81, J10.92, J10.93, J10.94, J10.95, J10.96, J10.105, J10.115, J10.120, J10.125, J10.130, J10.133, J10.134, J10.135, J10.136, J10.137, J10.140, J10.167, J10.168, J10.170, J10.171, J41.7, J42.7, J43.7, J44.7, J45.7, K1.12, K5.3, K6.10, K7.14, K9.14, K20.10, K22.10, K41.7, K42.7, K44.8, K45.7, K46.7, K47.7, L3.5, L12.16, L12.53, L14.5, L19.8, L20.10, L21.10, L22.10, L23.1, L24.1, L41.7, L42.7, L43.7, L44.7, L45.7, M1.4, M3.6, M7.14, M7.22, M9.14, M9.22, M41.4

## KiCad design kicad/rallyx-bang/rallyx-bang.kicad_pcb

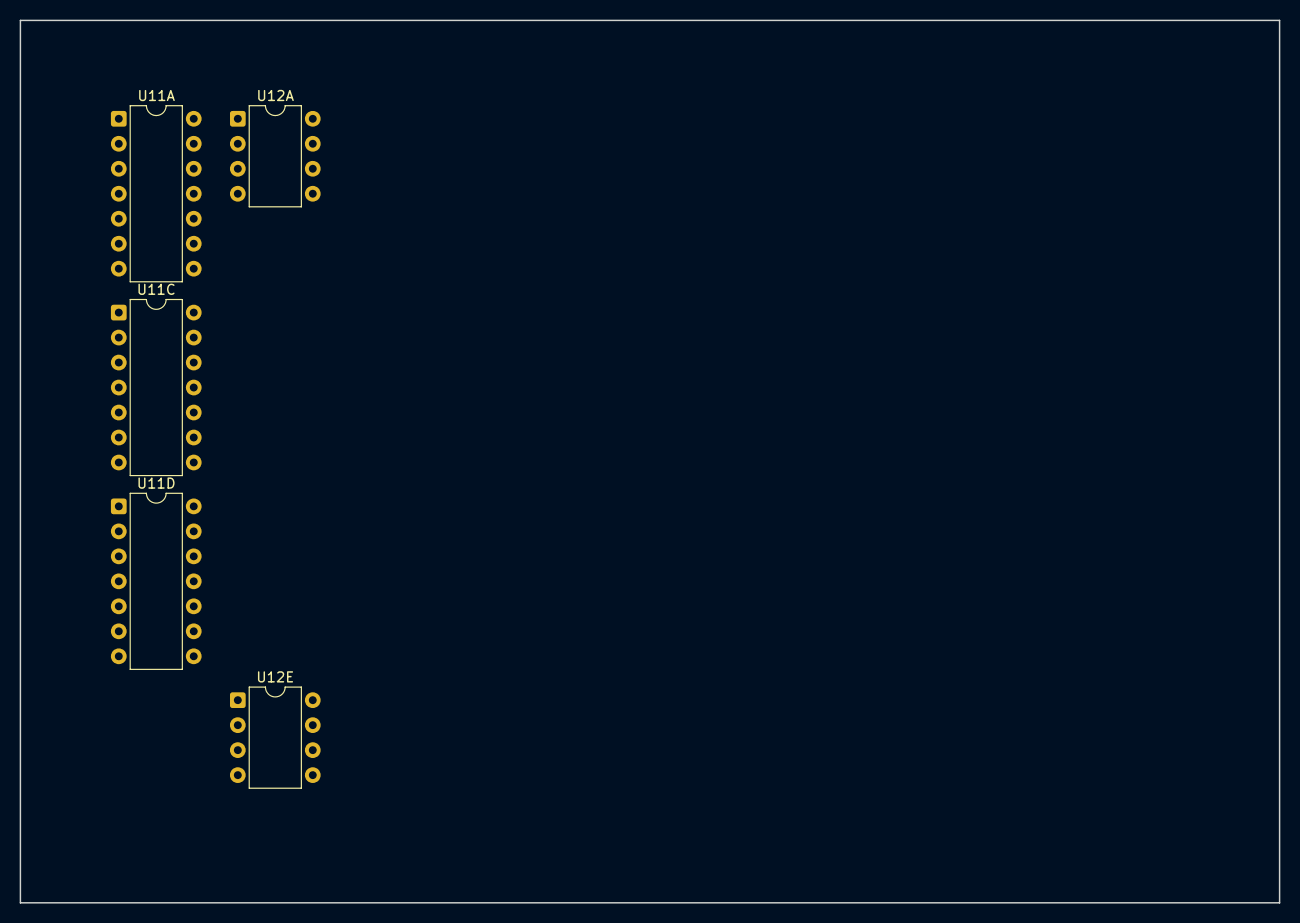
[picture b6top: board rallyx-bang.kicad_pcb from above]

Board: 2 copper layers, 128.0 x 89.7 mm, 5 parts (0 on the bottom side), 8 nets, no tracks yet.

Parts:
U11A: CD4006; DIP-14_W7.62mm
U11C: CD4070; DIP-14_W7.62mm
U11D: CD4066; DIP-14_W7.62mm
U12A: MB3730; DIP-8_W7.62mm
U12E: UA741; DIP-8_W7.62mm

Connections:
+5V: U11A.14, U11C.13, U11C.14, U11D.11, U11D.14
+12V: U12A.7, U12E.7
GND: U11A.7, U11C.5, U11C.6, U11C.7, U11C.8, U11C.9, U11D.3, U11D.4, U11D.5, U11D.6, U11D.7, U11D.8, U11D.9, U12A.4, U12E.4
unnamed: U11D.1, U11D.10
unnamed: U11A.1, U11A.12, U11C.2, U11D.13
unnamed: U11A.8, U11C.1
unnamed: U11A.6, U11A.10
unnamed: U11A.5, U11A.13

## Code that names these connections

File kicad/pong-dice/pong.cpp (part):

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static VIDEO_DESC( pong )
    VIDEO_RESISTANCE(1, K_OHM(1.0))
    VIDEO_RESISTANCE(2, K_OHM(1.2))
    VIDEO_RESISTANCE(Video::HBLANK_PIN, K_OHM(22.0))
    VIDEO_CONTRAST(2.0)
    VIDEO_RETRO_V_SIZE(246)
VIDEO_DESC_END
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    #define H64 "F9", 8
    #define H128 "F9", 11
    #define H256 "F6", 5
    #define H256_n "F6", 6
    #define HRESET "E7", 8
    #define HRESET_n "E7", 9


    // VRESET Circuit
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    #define V64 "E9", 8
    #define V128 "E9", 11
    #define V256 "D9", 5
    #define V256_n "D9", 6
    #define VRESET "E7", 6
    #define VRESET_n "E7", 5


    // HSync Logic
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    CONNECTION("H5", 8, "H5", 12)
    CONNECTION(H32, "H5", 13)

    #define HBLANK "H5", 8
    #define HBLANK_n "H5", 6

    // VSync Logic
    CONNECTION(VRESET, "F5", 8)
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    CONNECTION(V4, "G5", 2)
    CONNECTION("H5", 3, "G5", 13) 
    
    #define VBLANK "F5", 13
    #define VBLANK_n "F5", 10


    // Net circuit
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	
	CONNECTION("B2", 3, "E4", 9)
	
    #define SRST_n "COIN1", 1

    CONNECTION(SRST_n, "C9", 13)
	#define SRST "C9", 12    
	
    CONNECTION("LATCH", 2, SRST_n)
	CONNECTION("LATCH", 1, "E4", 8)

    #define RUN_n "LATCH", 3

	CONNECTION("B2", 3, "D2", 2)
	CONNECTION(RUN_n, "D2", 3)
	
	CONNECTION("D2", 1, "D1", 3)
	
    #define ATTRACT_n "D2", 1
    #define ATTRACT   "D1", 4

    // Game Control Logic			
	CONNECTION("H6", 6, "E6", 9)
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	CONNECTION("H7", 15, "H6", 12)
	CONNECTION("G6", 5, "H6", 13)

    #define HVID_n "H6", 8
	
	CONNECTION("H7", 15, "G5", 9)
	CONNECTION("G7", 15, "G5", 10)
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	CONNECTION(HVID_n, "H6", 4)
	CONNECTION(HVID_n, "H6", 5)
	
	#define HVID "H6", 6


	// Vertical Ball Counter
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	CONNECTION("E2", 6, "D2", 11)
	CONNECTION("E2", 6, "D2", 12)

    #define VVID_n "E2", 6
    #define VVID   "D2", 13


	// Hit Logic
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	CONNECTION("B2", 8, "B2", 12)
	CONNECTION("B2", 8, "B2", 13)
	
    #define HIT   "B2", 8
    #define HIT_n "B2", 11


    // Horizontal Ball Control
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    CONNECTION("VIDEO", 1, "E4", 12)
    CONNECTION("VIDEO", 2, "D3", 8)

    CONNECTION("VIDEO", Video::HBLANK_PIN, HBLANK)
    CONNECTION("VIDEO", Video::VBLANK_PIN, VBLANK)


    // Audio Summing
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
